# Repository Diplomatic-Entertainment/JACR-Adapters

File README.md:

# JACR-Adapters
Console Cartridge Adapters for use with the [Just Another Cartridge Reader](https://github.com/Diplomatic-Entertainment/JustAnotherCartridgeReader)

## All the files in this directory are licensed under the Attribution 4.0 International (CC BY 4.0)     

### This means that you are free to:    
- Share - copy and redistribute the material in any medium or format    
- Adapt - remix, transform, and build upon the material for any purpose, even commercially.  

The licensor cannot revoke these freedoms as long as you follow the license terms.    

### Under the following terms:    
- Attribution - You must give appropriate credit, provide a link to the license, and indicate if changes were made. You may do so in any reasonable manner, but not in any way that suggests the licensor endorses you or your use.    
- No additional restrictions - You may not apply legal terms or technological measures that legally restrict others from doing anything the license permits.    

More details: https://creativecommons.org/licenses/by/4.0/

##

You can view the schematic and PCB files using [KiCad](https://www.kicad.org/).

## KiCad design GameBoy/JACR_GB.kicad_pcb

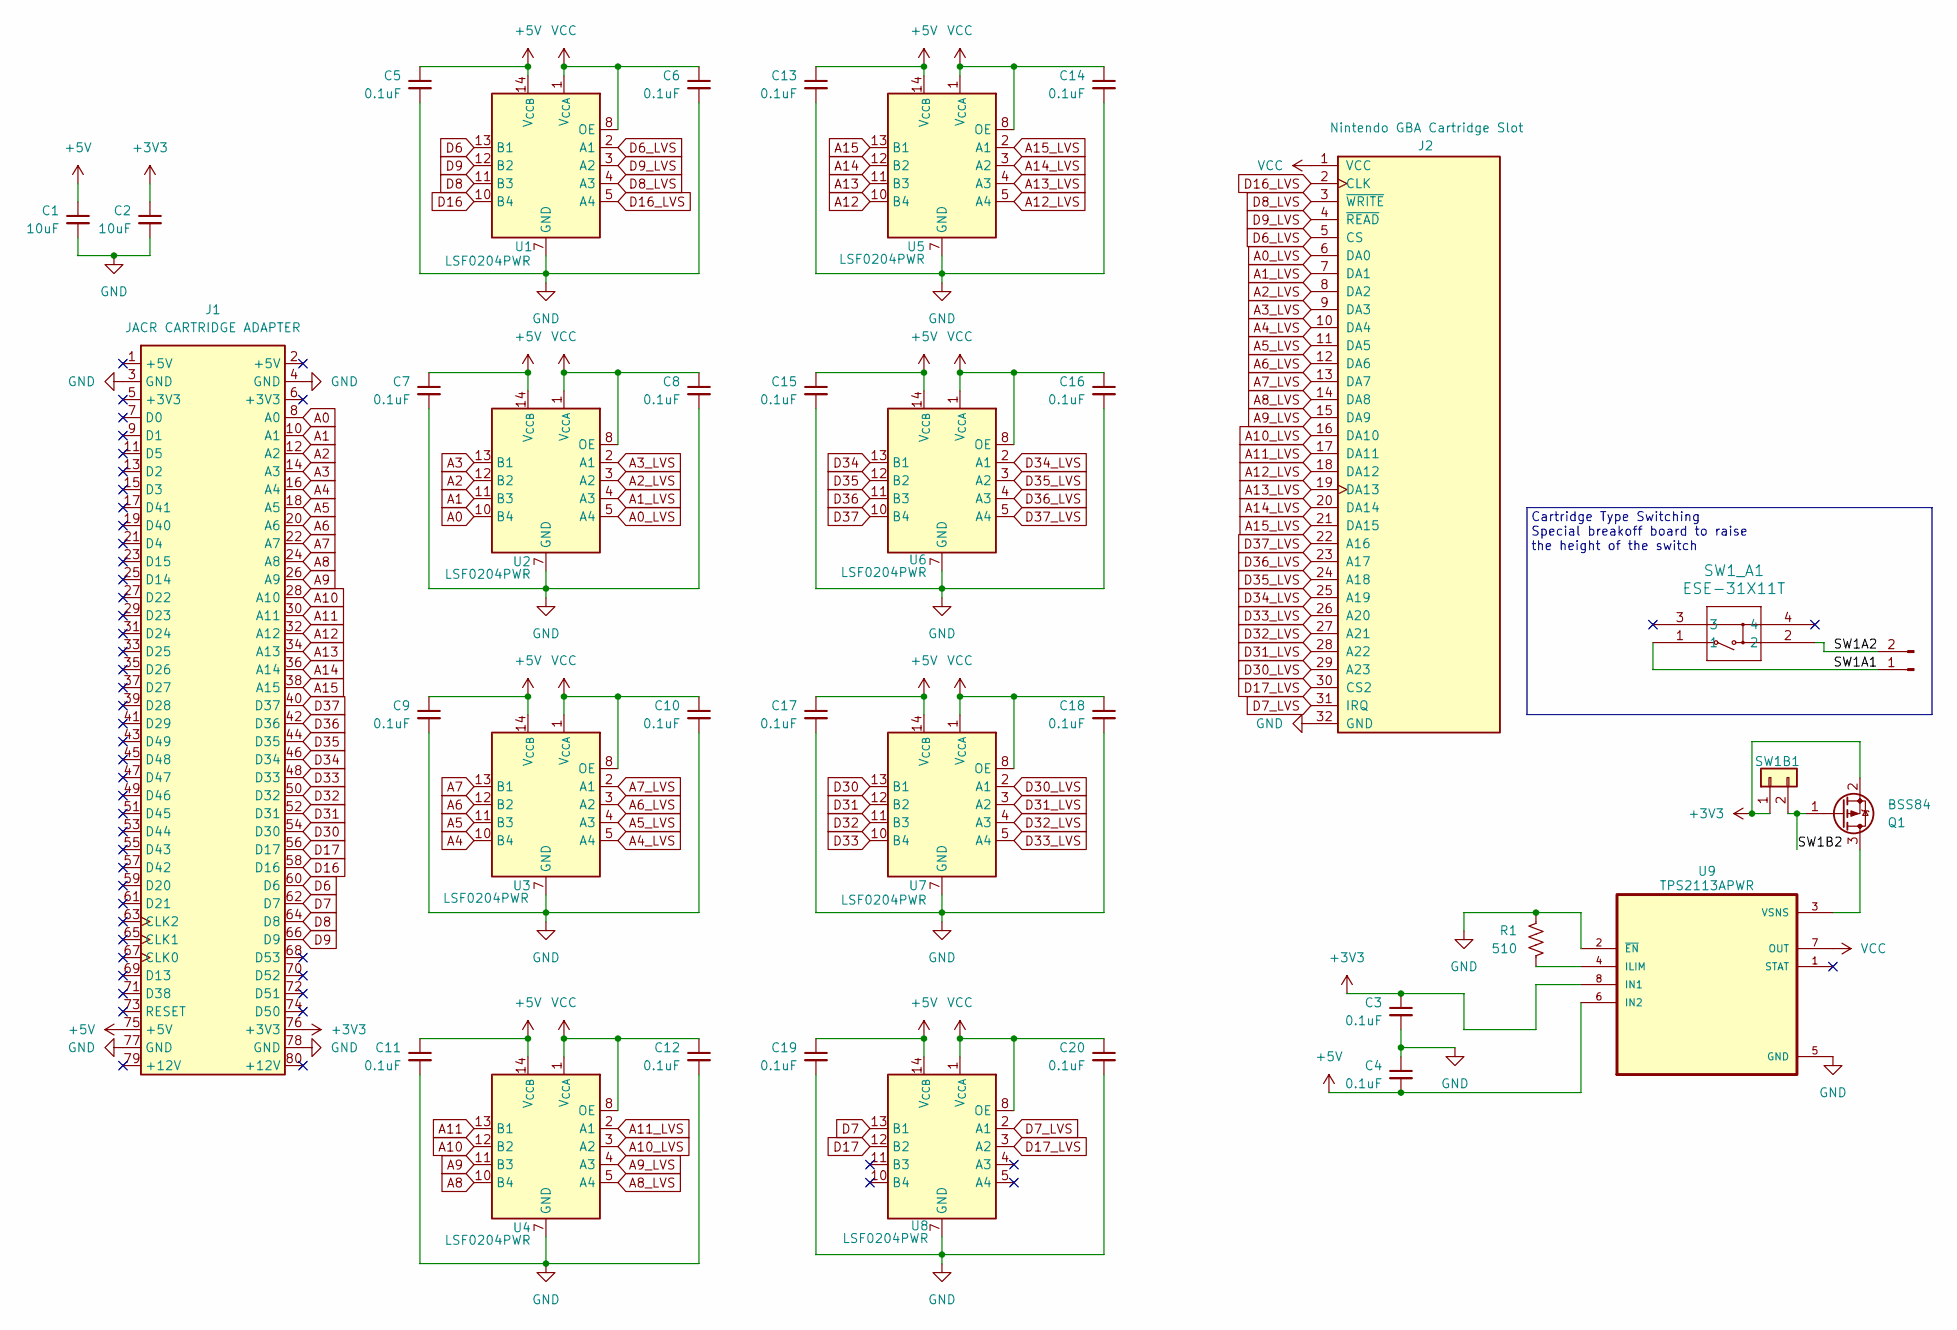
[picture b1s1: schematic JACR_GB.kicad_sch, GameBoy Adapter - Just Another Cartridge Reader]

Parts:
C1, C2: 10uF; C_0603_1608Metric_Pad1.08x0.95mm_HandSolder
C3, C4, C5, C6, C7, C8, C9, C10, C11, C12, C13, C14, C15, C16, C17, C18, C19, C20: 0.1uF; C_0603_1608Metric_Pad1.08x0.95mm_HandSolder
J1: JACR CARTRIDGE ADAPTER; JACR Cartridge Connector
J2: Nintendo GBA Cartridge Slot; GBA-SLOT-B
J3: Conn_01x02_Pin; SolderWire-0.1sqmm_1x02_P3.6mm_D0.4mm_OD1mm
Q1: BSS84; SOT-23
R1: 510; R_0603_1608Metric_Pad0.98x0.95mm_HandSolder
SW1B1: Conn_01x02; SolderWire-0.1sqmm_1x02_P3.6mm_D0.4mm_OD1mm
SW1_A1: ESE-31X11T; ESE-31R11T_PAN
U1, U2, U3, U4, U5, U6, U7, U8: LSF0204PWR; TSSOP-14_4.4x5mm_P0.65mm
U9: TPS2113APWR; TSSOP-8_4.4x3mm_P0.65mm

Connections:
+3V3: C2.1, C3.1, J1.76 (+3V3), Q1.2 (S), SW1B1.1, U9.8 (IN1); also elsewhere on the board
+5V: C1.1, C4.2, C5.1, C7.1, C9.1, C11.1, C13.1, C15.1, C17.1, C19.1, J1.75 (+5V), U1.14 (V_{CCB}), U2.14 (V_{CCB}), U3.14 (V_{CCB}), U4.14 (V_{CCB}), U5.14 (V_{CCB}), U6.14 (V_{CCB}), U7.14 (V_{CCB}), U8.14 (V_{CCB}), U9.6 (IN2)
/SW1A1: J3.1, SW1_A1.1; also elsewhere on the board
/SW1A2: J3.2, SW1_A1.2; also elsewhere on the board
/SW1B2: Q1.1 (G), SW1B1.2; also elsewhere on the board
A0: J1.8 (A0), U2.10 (B4)
A0_LVS: J2.6 (DA0), U2.5 (A4)
A1: J1.10 (A1), U2.11 (B3)
A1_LVS: J2.7 (DA1), U2.4 (A3)
A2: J1.12 (A2), U2.12 (B2)
A2_LVS: J2.8 (DA2), U2.3 (A2)
A3: J1.14 (A3), U2.13 (B1)
A3_LVS: J2.9 (DA3), U2.2 (A1)
A4: J1.16 (A4), U3.10 (B4)
A4_LVS: J2.10 (DA4), U3.5 (A4)
A5: J1.18 (A5), U3.11 (B3)
A5_LVS: J2.11 (DA5), U3.4 (A3)
A6: J1.20 (A6), U3.12 (B2)
A6_LVS: J2.12 (DA6), U3.3 (A2)
A7: J1.22 (A7), U3.13 (B1)
A7_LVS: J2.13 (DA7), U3.2 (A1)
A8: J1.24 (A8), U4.10 (B4)
A8_LVS: J2.14 (DA8), U4.5 (A4)
A9: J1.26 (A9), U4.11 (B3)
A9_LVS: J2.15 (DA9), U4.4 (A3)
A10: J1.28 (A10), U4.12 (B2)
A10_LVS: J2.16 (DA10), U4.3 (A2)
A11: J1.30 (A11), U4.13 (B1)
A11_LVS: J2.17 (DA11), U4.2 (A1)
A12: J1.32 (A12), U5.10 (B4)
A12_LVS: J2.18 (DA12), U5.5 (A4)
A13: J1.34 (A13), U5.11 (B3)
A13_LVS: J2.19 (DA13), U5.4 (A3)
A14: J1.36 (A14), U5.12 (B2)
A14_LVS: J2.20 (DA14), U5.3 (A2)
A15: J1.38 (A15), U5.13 (B1)
A15_LVS: J2.21 (DA15), U5.2 (A1)
D6: J1.60 (D6), U1.13 (B1)
D6_LVS: J2.5 (CS), U1.2 (A1)
D7: J1.62 (D7), U8.13 (B1)
D7_LVS: J2.31 (IRQ), U8.2 (A1)
D8: J1.64 (D8), U1.11 (B3)
D8_LVS: J2.3 (~WRITE), U1.4 (A3)
D9: J1.66 (D9), U1.12 (B2)
D9_LVS: J2.4 (~READ), U1.3 (A2)
D16: J1.58 (D16), U1.10 (B4)
D16_LVS: J2.2 (CLK), U1.5 (A4)
D17: J1.56 (D17), U8.12 (B2)
D17_LVS: J2.30 (CS2), U8.3 (A2)
D30: J1.54 (D30), U7.13 (B1)
D30_LVS: J2.29 (A23), U7.2 (A1)
D31: J1.52 (D31), U7.12 (B2)
D31_LVS: J2.28 (A22), U7.3 (A2)
D32: J1.50 (D32), U7.11 (B3)
D32_LVS: J2.27 (A21), U7.4 (A3)
D33: J1.48 (D33), U7.10 (B4)
D33_LVS: J2.26 (A20), U7.5 (A4)
D34: J1.46 (D34), U6.13 (B1)
D34_LVS: J2.25 (A19), U6.2 (A1)
D35: J1.44 (D35), U6.12 (B2)
D35_LVS: J2.24 (A18), U6.3 (A2)
D36: J1.42 (D36), U6.11 (B3)
D36_LVS: J2.23 (A17), U6.4 (A3)
D37: J1.40 (D37), U6.10 (B4)
D37_LVS: J2.22 (A16), U6.5 (A4)
GND: C1.2, C2.2, C3.2, C4.1, C5.2, C6.2, C7.2, C8.2, C9.2, C10.2, C11.2, C12.2, C13.2, C14.2, C15.2, C16.2, C17.2, C18.2, C19.2, C20.2, J1.3 (GND), J1.4 (GND), J1.77 (GND), J1.78 (GND), J2.32 (GND), R1.1, U1.7 (GND), U2.7 (GND), U3.7 (GND), U4.7 (GND), U5.7 (GND), U6.7 (GND), U7.7 (GND), U8.7 (GND), U9.2 (~EN), U9.5 (GND)
unnamed: Q1.3 (D), U9.3 (VSNS)
unnamed: R1.2, U9.4 (ILIM)
VCC: C6.1, C8.1, C10.1, C12.1, C14.1, C16.1, C18.1, C20.1, J2.1 (VCC), U1.1 (V_{CCA}), U1.8 (OE), U2.1 (V_{CCA}), U2.8 (OE), U3.1 (V_{CCA}), U3.8 (OE), U4.1 (V_{CCA}), U4.8 (OE), U5.1 (V_{CCA}), U5.8 (OE), U6.1 (V_{CCA}), U6.8 (OE), U7.1 (V_{CCA}), U7.8 (OE), U8.1 (V_{CCA}), U8.8 (OE), U9.7 (OUT)

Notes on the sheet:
Cartridge Type Switching Special breakoff board to raise the height of the switch

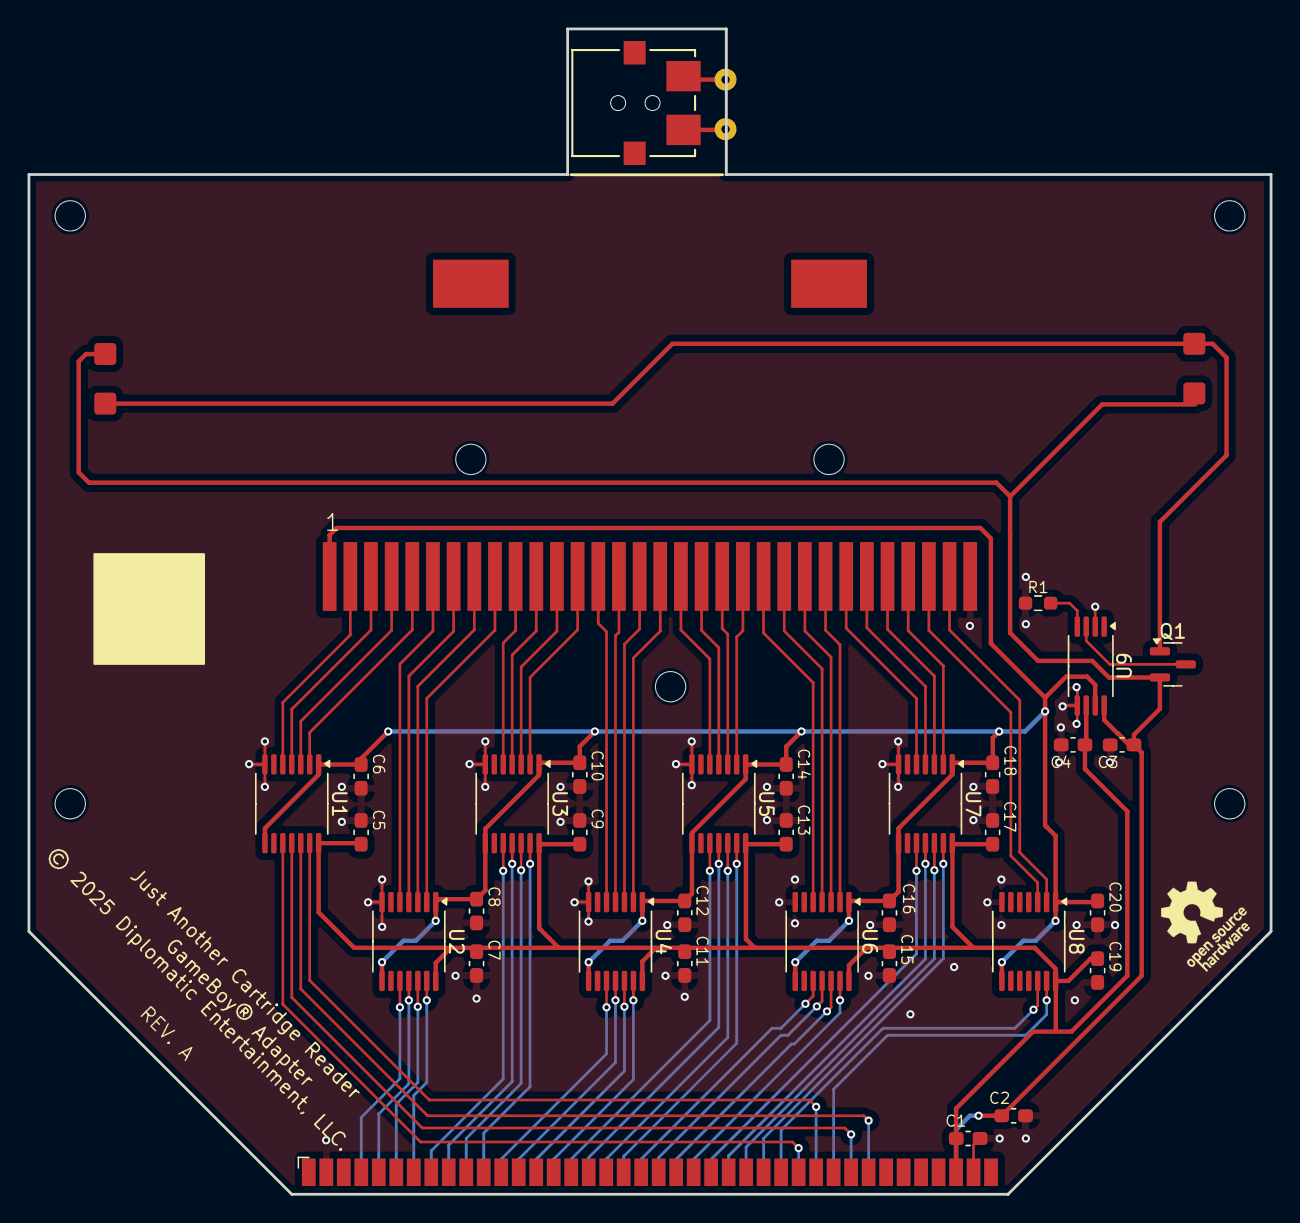
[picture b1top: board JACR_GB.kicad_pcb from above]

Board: 2 copper layers, 90.2 x 84.6 mm, 38 parts (0 on the bottom side), 69 nets.

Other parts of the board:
BAR**: 2D Barcode 8mm
SW1A1, SW1B1#2: Conn_01x02; SolderWire-0.1sqmm_1x02_P3.6mm_D0.4mm_OD1mm

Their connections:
+3V3: SW1B1#2.1; also elsewhere on the board
/SW1A1: SW1A1.1; also elsewhere on the board
/SW1A2: SW1A1.2; also elsewhere on the board
/SW1B2: SW1B1#2.2; also elsewhere on the board

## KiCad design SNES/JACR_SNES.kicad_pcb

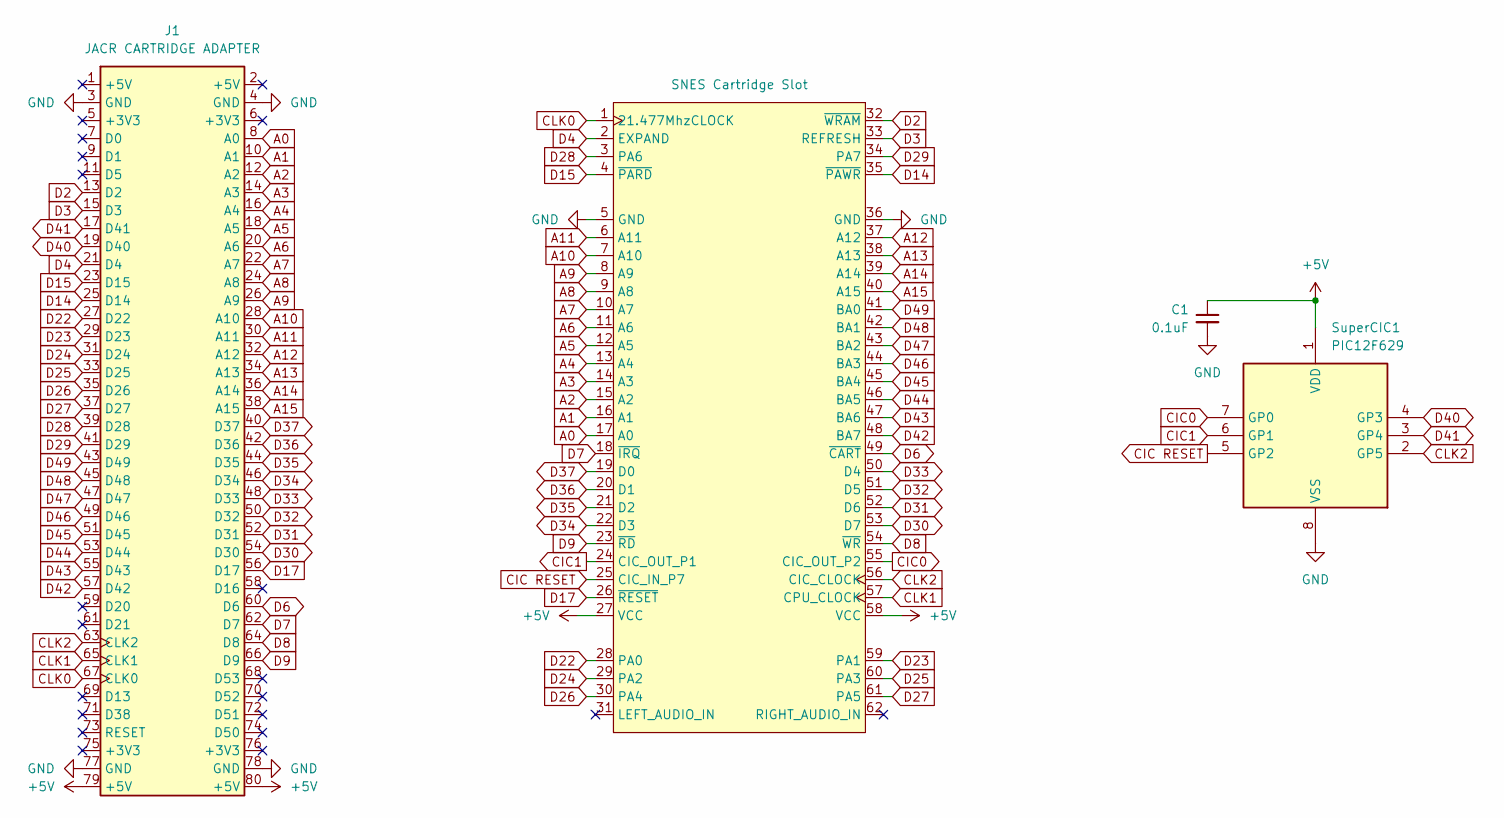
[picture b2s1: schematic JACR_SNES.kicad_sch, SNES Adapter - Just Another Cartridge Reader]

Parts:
C1: 0.1uF; C_0603_1608Metric_Pad1.08x0.95mm_HandSolder
J1: JACR CARTRIDGE ADAPTER; JACR Cartridge Connector
J2: SNES Cartridge Slot; SNES Cartridge Connector 62PIN 2.5mm CardEdge
SuperCIC1: PIC12F629; SOIC-8_3.9x4.9mm_P1.27mm

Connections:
+5V: C1.1, J1.79 (+5V), J1.80 (+5V), J2.27 (VCC), J2.58 (VCC), SuperCIC1.1 (VDD)
A0: J1.8 (A0), J2.17 (A0)
A1: J1.10 (A1), J2.16 (A1)
A2: J1.12 (A2), J2.15 (A2)
A3: J1.14 (A3), J2.14 (A3)
A4: J1.16 (A4), J2.13 (A4)
A5: J1.18 (A5), J2.12 (A5)
A6: J1.20 (A6), J2.11 (A6)
A7: J1.22 (A7), J2.10 (A7)
A8: J1.24 (A8), J2.9 (A8)
A9: J1.26 (A9), J2.8 (A9)
A10: J1.28 (A10), J2.7 (A10)
A11: J1.30 (A11), J2.6 (A11)
A12: J1.32 (A12), J2.37 (A12)
A13: J1.34 (A13), J2.38 (A13)
A14: J1.36 (A14), J2.39 (A14)
A15: J1.38 (A15), J2.40 (A15)
CIC0: J2.55 (CIC_OUT_P2), SuperCIC1.7 (GP0)
CIC1: J2.24 (CIC_OUT_P1), SuperCIC1.6 (GP1)
CIC RESET: J2.25 (CIC_IN_P7), SuperCIC1.5 (GP2)
CLK0: J1.67 (CLK0), J2.1 (21.477MhzCLOCK)
CLK1: J1.65 (CLK1), J2.57 (CPU_CLOCK)
CLK2: J1.63 (CLK2), J2.56 (CIC_CLOCK), SuperCIC1.2 (GP5)
D2: J1.13 (D2), J2.32 (~WRAM)
D3: J1.15 (D3), J2.33 (REFRESH)
D4: J1.21 (D4), J2.2 (EXPAND)
D6: J1.60 (D6), J2.49 (~CART)
D7: J1.62 (D7), J2.18 (~IRQ)
D8: J1.64 (D8), J2.54 (~WR)
D9: J1.66 (D9), J2.23 (~RD)
D14: J1.25 (D14), J2.35 (~PAWR)
D15: J1.23 (D15), J2.4 (~PARD)
D17: J1.56 (D17), J2.26 (~RESET)
D22: J1.27 (D22), J2.28 (PA0)
D23: J1.29 (D23), J2.59 (PA1)
D24: J1.31 (D24), J2.29 (PA2)
D25: J1.33 (D25), J2.60 (PA3)
D26: J1.35 (D26), J2.30 (PA4)
D27: J1.37 (D27), J2.61 (PA5)
D28: J1.39 (D28), J2.3 (PA6)
D29: J1.41 (D29), J2.34 (PA7)
D30: J1.54 (D30), J2.53 (D7)
D31: J1.52 (D31), J2.52 (D6)
D32: J1.50 (D32), J2.51 (D5)
D33: J1.48 (D33), J2.50 (D4)
D34: J1.46 (D34), J2.22 (D3)
D35: J1.44 (D35), J2.21 (D2)
D36: J1.42 (D36), J2.20 (D1)
D37: J1.40 (D37), J2.19 (D0)
D40: J1.19 (D40), SuperCIC1.4 (GP3)
D41: J1.17 (D41), SuperCIC1.3 (GP4)
D42: J1.57 (D42), J2.48 (BA7)
D43: J1.55 (D43), J2.47 (BA6)
D44: J1.53 (D44), J2.46 (BA5)
D45: J1.51 (D45), J2.45 (BA4)
D46: J1.49 (D46), J2.44 (BA3)
D47: J1.47 (D47), J2.43 (BA2)
D48: J1.45 (D48), J2.42 (BA1)
D49: J1.43 (D49), J2.41 (BA0)
GND: C1.2, J1.3 (GND), J1.4 (GND), J1.77 (GND), J1.78 (GND), J2.5 (GND), J2.36 (GND), SuperCIC1.8 (VSS)

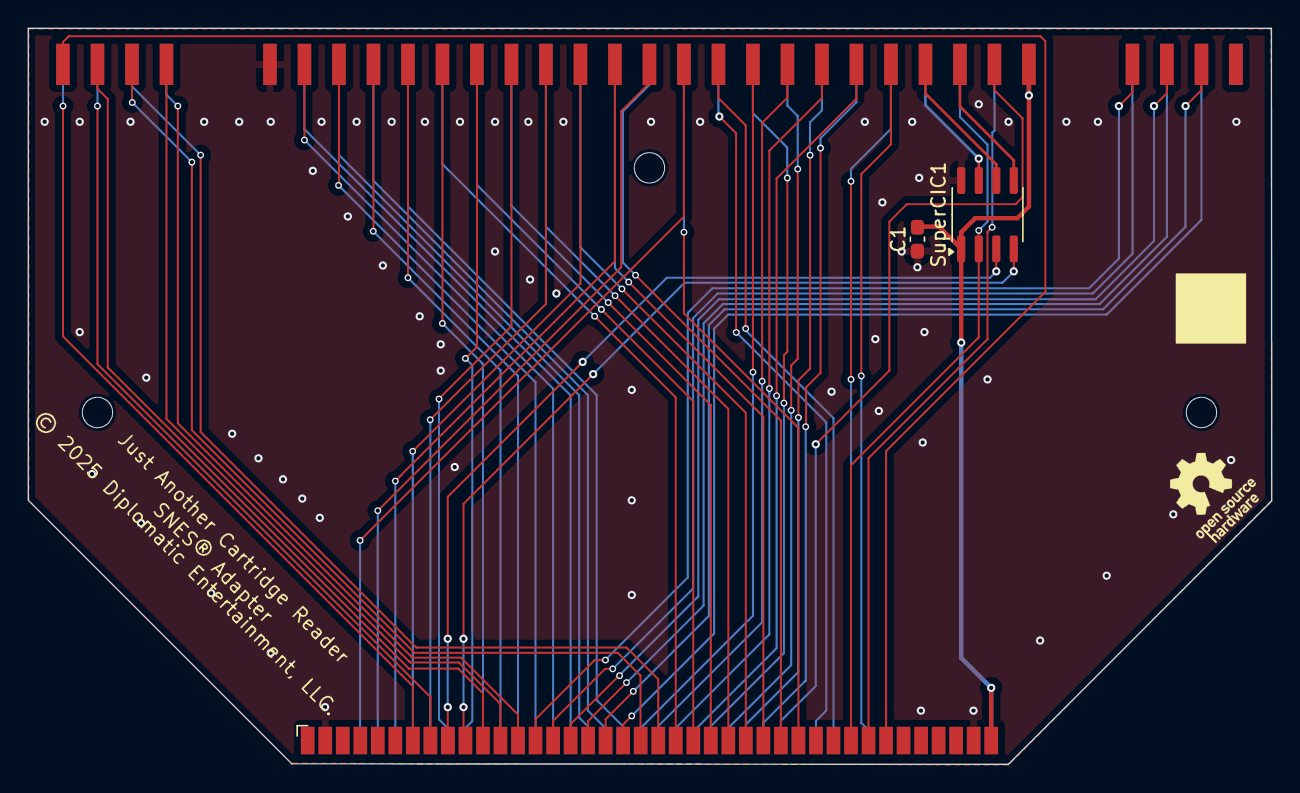
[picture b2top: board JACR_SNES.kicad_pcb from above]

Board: 2 copper layers, 90.1 x 53.3 mm, 5 parts (0 on the bottom side), 60 nets.

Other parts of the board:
BAR***: 2D Barcode 5mm

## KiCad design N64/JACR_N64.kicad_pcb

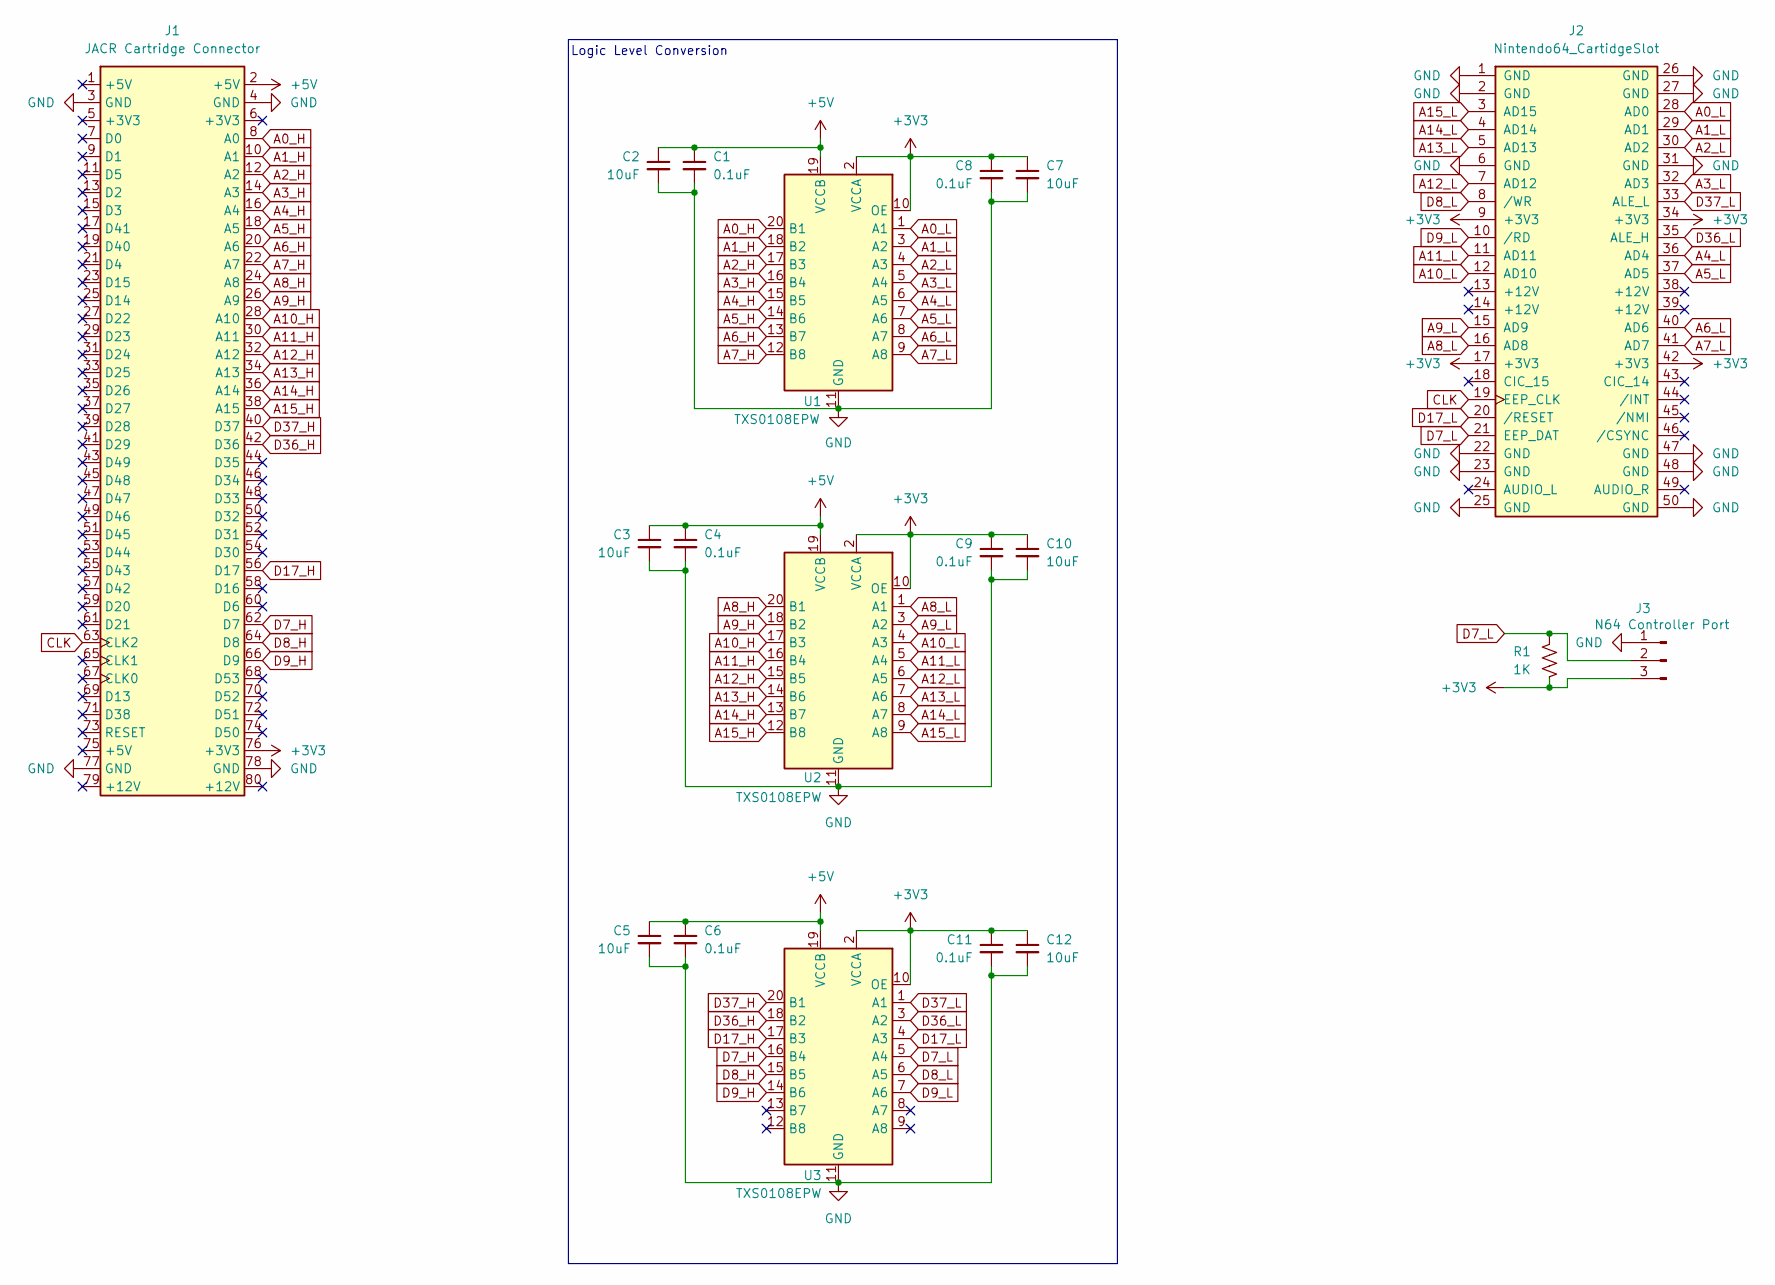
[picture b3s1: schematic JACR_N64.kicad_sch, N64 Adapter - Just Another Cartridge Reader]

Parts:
C1, C4, C6, C8, C9, C11: 0.1uF; C_0603_1608Metric_Pad1.08x0.95mm_HandSolder
C2, C3, C5, C7, C10, C12: 10uF; C_0603_1608Metric_Pad1.08x0.95mm_HandSolder
J1: JACR Cartridge Connector; PinHeader 2x40 P1.27mm
J2: Nintendo64_CartidgeSlot; N64_Cartridge_Connector_50PIN_2.5mm_CardEdge
J3: N64 Controller Port
R1: 1K; R_0603_1608Metric
U1, U2, U3: TXS0108EPW; TSSOP-20_4.4x6.5mm_P0.65mm

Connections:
+3V3: C7.1, C8.1, C9.1, C10.1, C11.1, C12.1, J1.76 (+3V3), J2.9 (+3V3), J2.17 (+3V3), J2.34 (+3V3), J2.42 (+3V3), J3.3, R1.2, U1.2 (VCCA), U1.10 (OE), U2.2 (VCCA), U2.10 (OE), U3.2 (VCCA), U3.10 (OE); also elsewhere on the board
+5V: C1.1, C2.1, C3.1, C4.1, C5.1, C6.1, J1.2 (+5V), U1.19 (VCCB), U2.19 (VCCB), U3.19 (VCCB)
A0_H: J1.8 (A0), U1.20 (B1)
A0_L: J2.28 (AD0), U1.1 (A1)
A1_H: J1.10 (A1), U1.18 (B2)
A1_L: J2.29 (AD1), U1.3 (A2)
A2_H: J1.12 (A2), U1.17 (B3)
A2_L: J2.30 (AD2), U1.4 (A3)
A3_H: J1.14 (A3), U1.16 (B4)
A3_L: J2.32 (AD3), U1.5 (A4)
A4_H: J1.16 (A4), U1.15 (B5)
A4_L: J2.36 (AD4), U1.6 (A5)
A5_H: J1.18 (A5), U1.14 (B6)
A5_L: J2.37 (AD5), U1.7 (A6)
A6_H: J1.20 (A6), U1.13 (B7)
A6_L: J2.40 (AD6), U1.8 (A7)
A7_H: J1.22 (A7), U1.12 (B8)
A7_L: J2.41 (AD7), U1.9 (A8)
A8_H: J1.24 (A8), U2.20 (B1)
A8_L: J2.16 (AD8), U2.1 (A1)
A9_H: J1.26 (A9), U2.18 (B2)
A9_L: J2.15 (AD9), U2.3 (A2)
A10_H: J1.28 (A10), U2.17 (B3)
A10_L: J2.12 (AD10), U2.4 (A3)
A11_H: J1.30 (A11), U2.16 (B4)
A11_L: J2.11 (AD11), U2.5 (A4)
A12_H: J1.32 (A12), U2.15 (B5)
A12_L: J2.7 (AD12), U2.6 (A5)
A13_H: J1.34 (A13), U2.14 (B6)
A13_L: J2.5 (AD13), U2.7 (A6)
A14_H: J1.36 (A14), U2.13 (B7)
A14_L: J2.4 (AD14), U2.8 (A7)
A15_H: J1.38 (A15), U2.12 (B8)
A15_L: J2.3 (AD15), U2.9 (A8)
CLK: J1.63 (CLK2), J2.19 (EEP_CLK)
D7_H: J1.62 (D7), U3.16 (B4)
D7_L: J2.21 (EEP_DAT), J3.2, R1.1, U3.5 (A4); also elsewhere on the board
D8_H: J1.64 (D8), U3.15 (B5)
D8_L: J2.8 (/WR), U3.6 (A5)
D9_H: J1.66 (D9), U3.14 (B6)
D9_L: J2.10 (/RD), U3.7 (A6)
D17_H: J1.56 (D17), U3.17 (B3)
D17_L: J2.20 (/RESET), U3.4 (A3)
D36_H: J1.42 (D36), U3.18 (B2)
D36_L: J2.35 (ALE_H), U3.3 (A2)
D37_H: J1.40 (D37), U3.20 (B1)
D37_L: J2.33 (ALE_L), U3.1 (A1)
GND: C1.2, C2.2, C3.2, C4.2, C5.2, C6.2, C7.2, C8.2, C9.2, C10.2, C11.2, C12.2, J1.3 (GND), J1.4 (GND), J1.77 (GND), J1.78 (GND), J2.1 (GND), J2.2 (GND), J2.6 (GND), J2.22 (GND), J2.23 (GND), J2.25 (GND), J2.26 (GND), J2.27 (GND), J2.31 (GND), J2.47 (GND), J2.48 (GND), J2.50 (GND), J3.1, U1.11 (GND), U2.11 (GND), U3.11 (GND); also elsewhere on the board

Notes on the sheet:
Logic Level Conversion

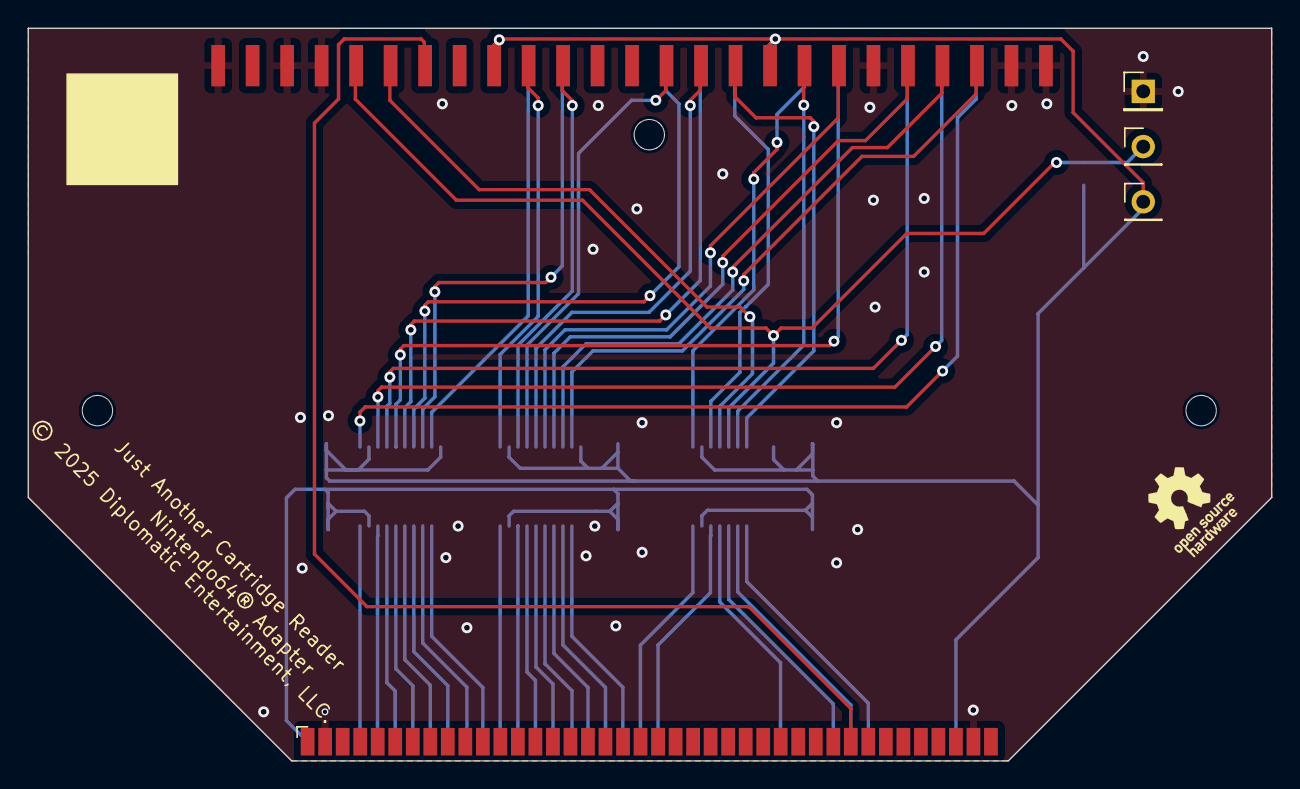
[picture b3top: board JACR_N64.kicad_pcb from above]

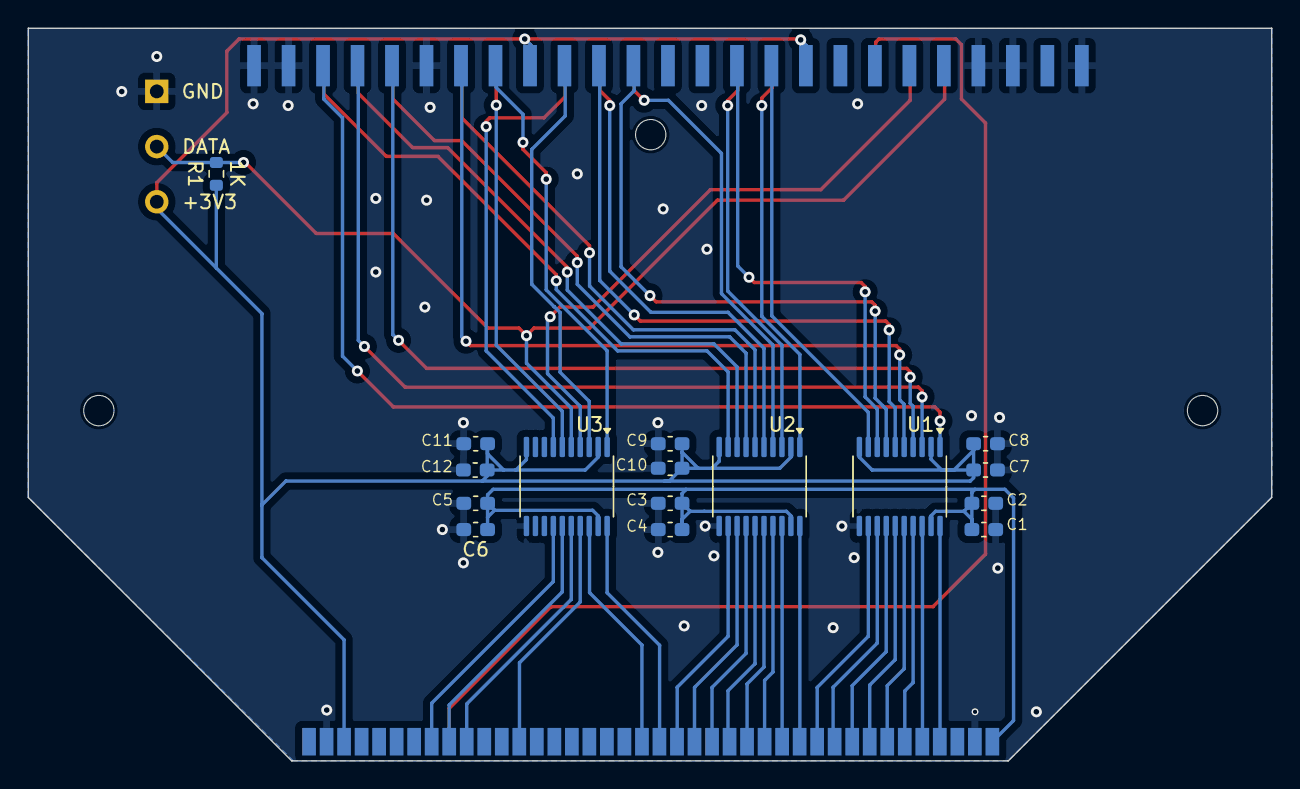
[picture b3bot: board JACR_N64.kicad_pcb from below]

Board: 2 copper layers, 90.1 x 53.1 mm, 22 parts (16 on the bottom side), 48 nets.

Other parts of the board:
BAR**: 2D Barcode 8mm
PIN_1: GND; PinHeader_1x01_P2.54mm_Vertical
Pin_02: DATA; PinHeader_1x01_P2.54mm_Vertical
Pin_3: +3V3; PinHeader_1x01_P2.54mm_Vertical

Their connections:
+3V3: Pin_3.3 (Pin_1); also elsewhere on the board
D7_L: Pin_02.2 (Pin_1); also elsewhere on the board
GND: PIN_1.1; also elsewhere on the board

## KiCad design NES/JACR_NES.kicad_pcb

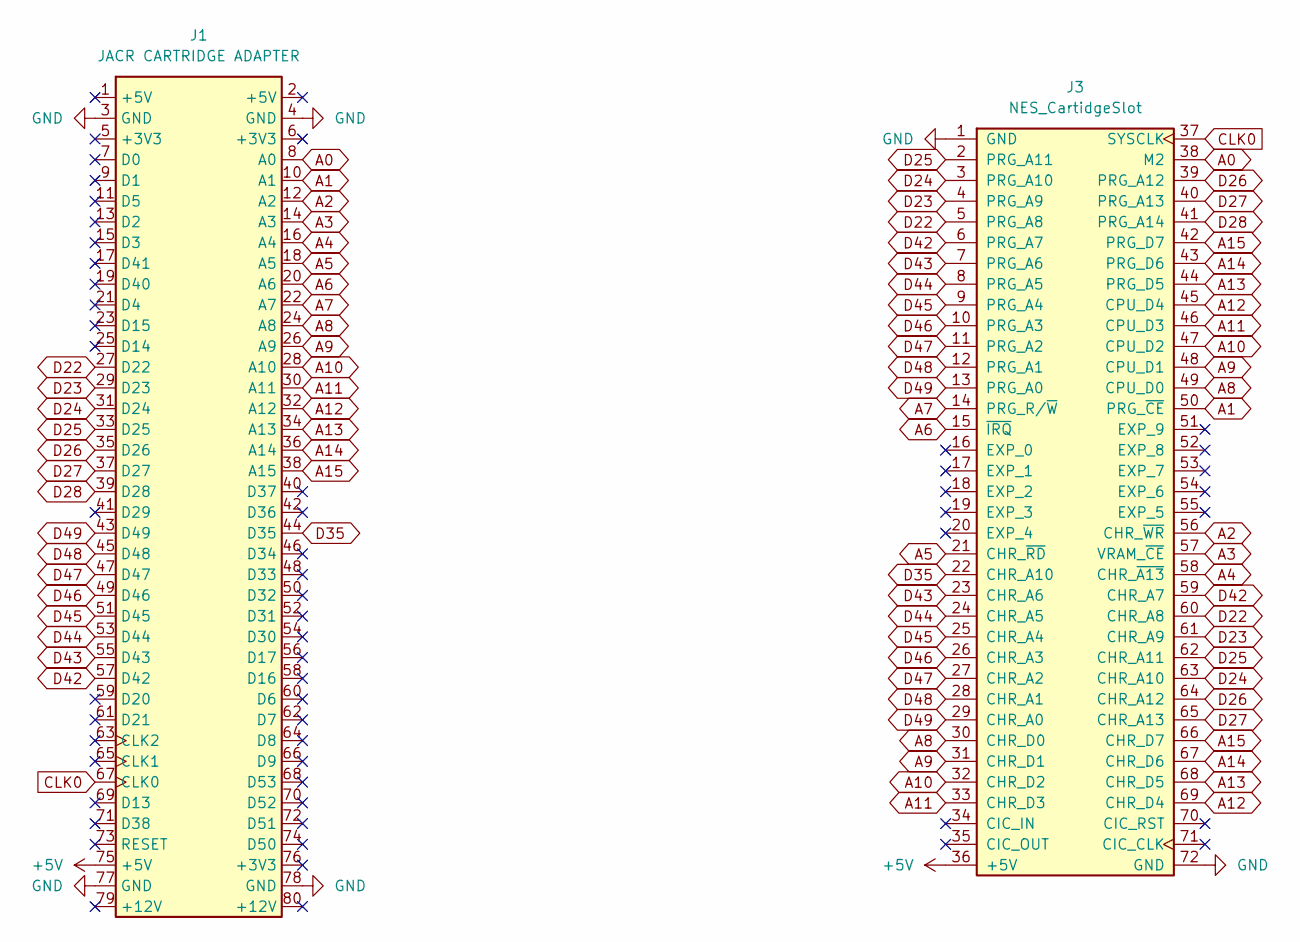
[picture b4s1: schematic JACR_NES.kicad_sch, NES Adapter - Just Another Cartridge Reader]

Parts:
J1: JACR CARTRIDGE ADAPTER; JACR Cartridge Connector
J3: NES_CartidgeSlot; NES_Cartridge_Connector_72PIN_2.5mm_CardEdge

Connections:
+5V: J1.75 (+5V), J3.36 (+5V)
A0: J1.8 (A0), J3.38 (M2)
A1: J1.10 (A1), J3.50 (PRG_~CE)
A2: J1.12 (A2), J3.56 (CHR_~WR)
A3: J1.14 (A3), J3.57 (VRAM_~CE)
A4: J1.16 (A4), J3.58 (CHR_~A13)
A5: J1.18 (A5), J3.21 (CHR_~RD)
A6: J1.20 (A6), J3.15 (~IRQ)
A7: J1.22 (A7), J3.14 (PRG_R/~W)
A8: J1.24 (A8), J3.30 (CHR_D0), J3.49 (CPU_D0)
A9: J1.26 (A9), J3.31 (CHR_D1), J3.48 (CPU_D1)
A10: J1.28 (A10), J3.32 (CHR_D2), J3.47 (CPU_D2)
A11: J1.30 (A11), J3.33 (CHR_D3), J3.46 (CPU_D3)
A12: J1.32 (A12), J3.45 (CPU_D4), J3.69 (CHR_D4)
A13: J1.34 (A13), J3.44 (PRG_D5), J3.68 (CHR_D5)
A14: J1.36 (A14), J3.43 (PRG_D6), J3.67 (CHR_D6)
A15: J1.38 (A15), J3.42 (PRG_D7), J3.66 (CHR_D7)
CLK0: J1.67 (CLK0), J3.37 (SYSCLK)
D22: J1.27 (D22), J3.5 (PRG_A8), J3.60 (CHR_A8)
D23: J1.29 (D23), J3.4 (PRG_A9), J3.61 (CHR_A9)
D24: J1.31 (D24), J3.3 (PRG_A10), J3.63 (CHR_A10)
D25: J1.33 (D25), J3.2 (PRG_A11), J3.62 (CHR_A11)
D26: J1.35 (D26), J3.39 (PRG_A12), J3.64 (CHR_A12)
D27: J1.37 (D27), J3.40 (PRG_A13), J3.65 (CHR_A13)
D28: J1.39 (D28), J3.41 (PRG_A14)
D35: J1.44 (D35), J3.22 (CHR_A10)
D42: J1.57 (D42), J3.6 (PRG_A7), J3.59 (CHR_A7)
D43: J1.55 (D43), J3.7 (PRG_A6), J3.23 (CHR_A6)
D44: J1.53 (D44), J3.8 (PRG_A5), J3.24 (CHR_A5)
D45: J1.51 (D45), J3.9 (PRG_A4), J3.25 (CHR_A4)
D46: J1.49 (D46), J3.10 (PRG_A3), J3.26 (CHR_A3)
D47: J1.47 (D47), J3.11 (PRG_A2), J3.27 (CHR_A2)
D48: J1.45 (D48), J3.12 (PRG_A1), J3.28 (CHR_A1)
D49: J1.43 (D49), J3.13 (PRG_A0), J3.29 (CHR_A0)
GND: J1.3 (GND), J1.4 (GND), J1.77 (GND), J1.78 (GND), J3.1 (GND), J3.72 (GND)

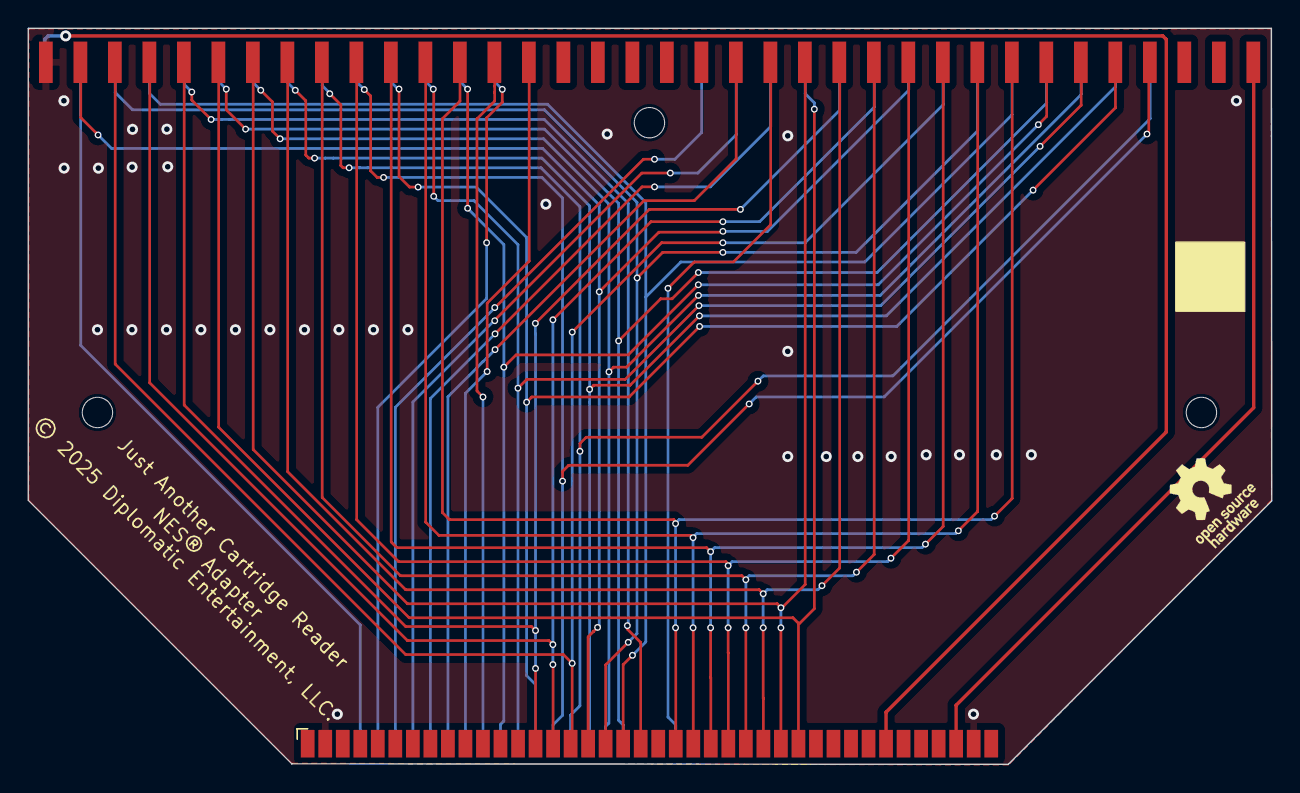
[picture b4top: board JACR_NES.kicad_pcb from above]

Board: 2 copper layers, 90.1 x 53.3 mm, 3 parts (0 on the bottom side), 35 nets.

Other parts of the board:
BAR***: 2D Barcode 5mm

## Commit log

2025-10-22 updated Git files
    added fab files to the ignore list
    updated read me
2025-10-22 KiCad Libraries
    Custom created Symbols and Components
2025-10-22 NES Adapter
    Currently untested however
2025-10-22 SNES Adapter
    SNES Adapter - untested at this time
2025-10-22 N64 Adapter
2025-10-22 JACR connector was modified, voltage pins were changed
2025-10-23 Updated Images and PDF for SNES Change
2025-10-23 Virtual Boy Adapter
2025-10-23 GameBoy Adapter

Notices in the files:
GameBoy/JACR_GB.kicad_pcb:
© 2025 Diplomatic Entertainment, LLC.
